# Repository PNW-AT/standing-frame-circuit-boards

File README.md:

https://github.com/PNW-AT/standing-frame-circuit-boards

https://github.com/PNW-AT/standing-frame

# Acknowledgements 
* Made using a [PJRC Teensy 4.1](https://www.pjrc.com/store/teensy41.html)
* https://github.com/XenGi/teensy.pretty
* https://github.com/XenGi/teensy_library

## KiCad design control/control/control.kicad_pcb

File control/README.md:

PCB CAD for the user interface panel

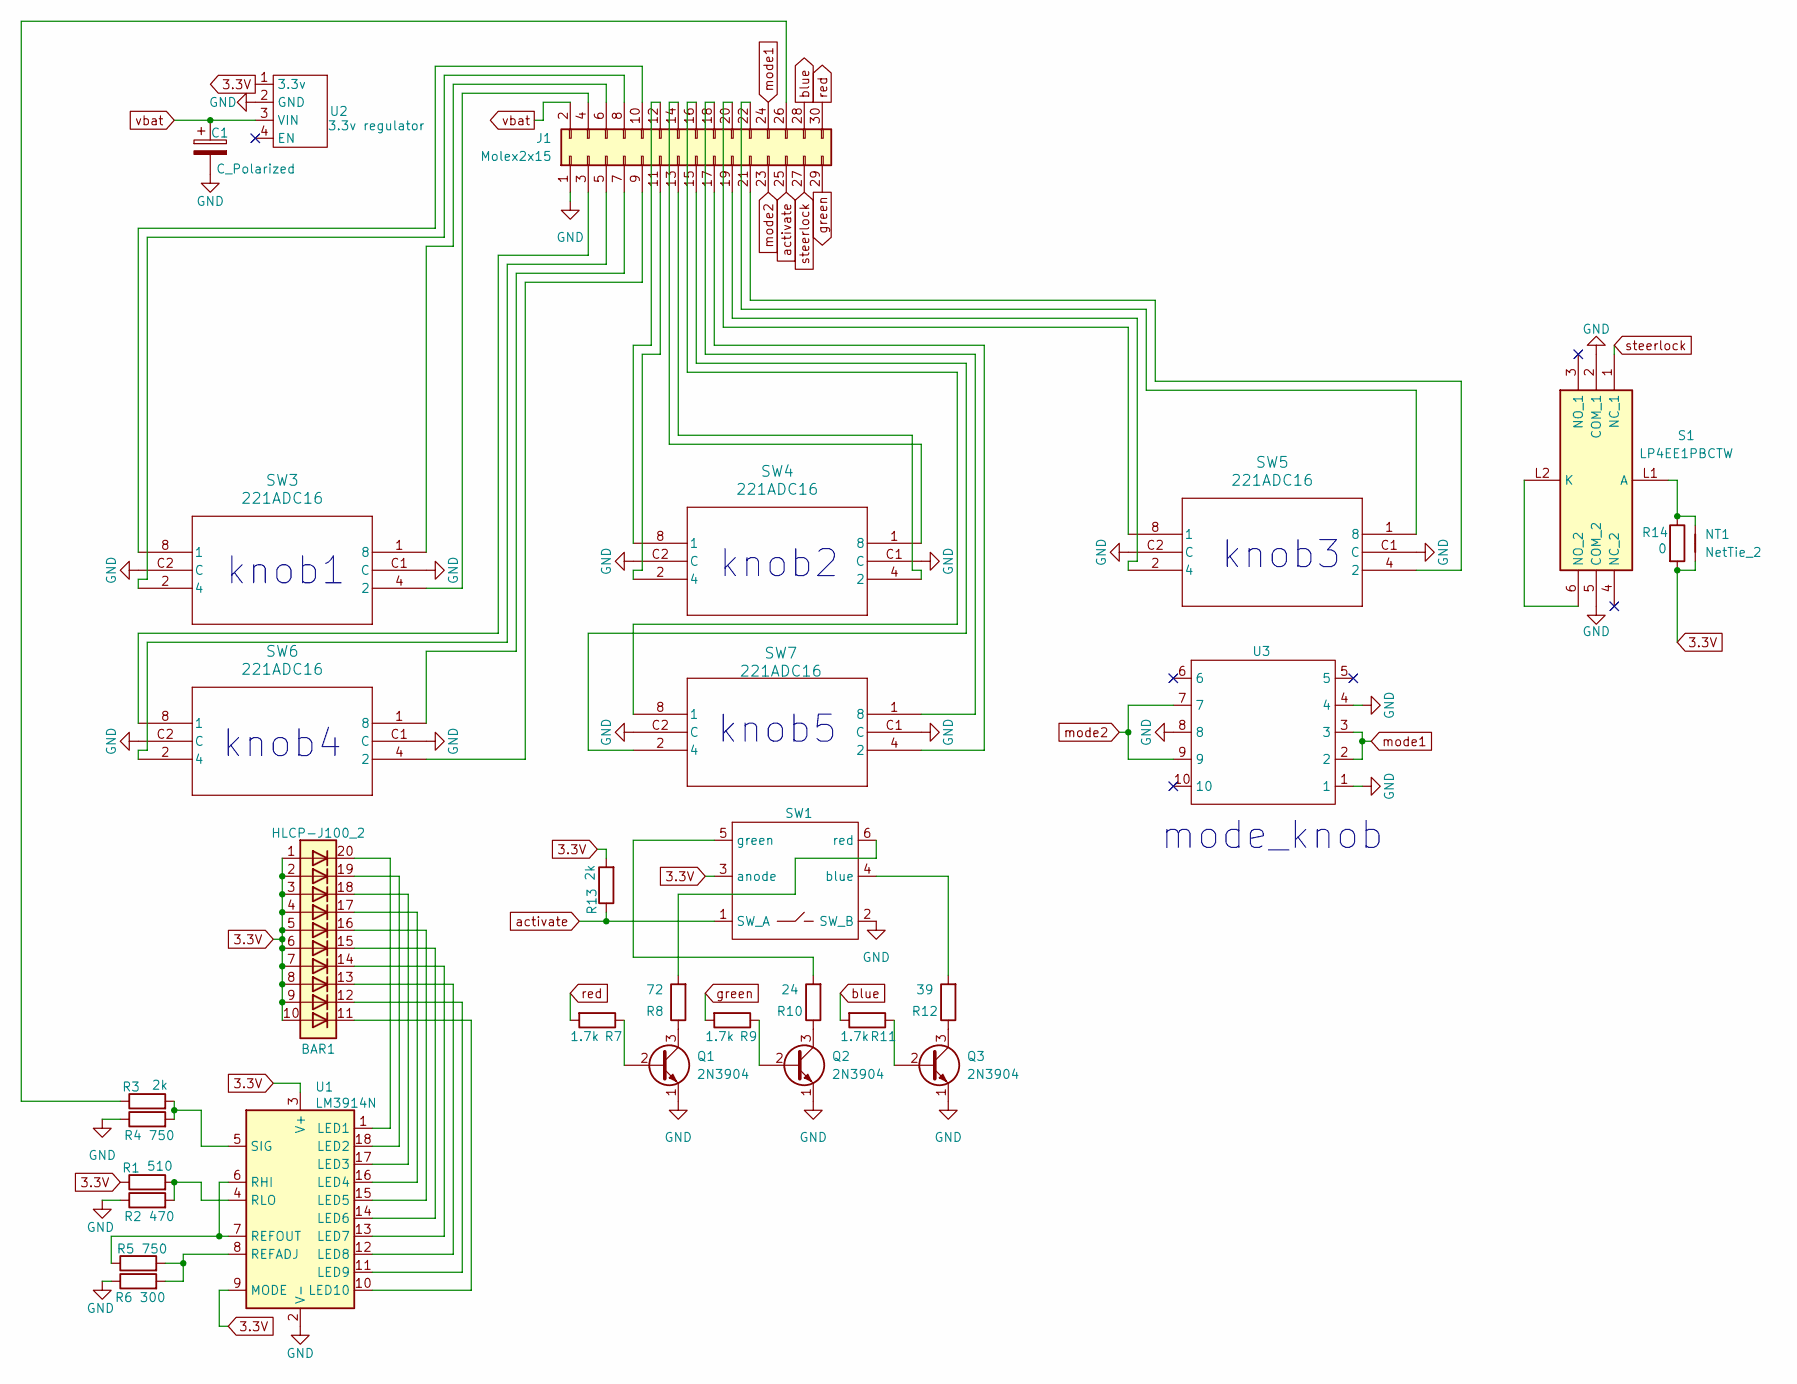
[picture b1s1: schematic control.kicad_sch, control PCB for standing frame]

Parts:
BAR1: HLCP-J100_2; HLCP-J100
C1: C_Polarized; C_Radial_D8.0mm_H11.5mm_P3.50mm
J1: Molex2x15; CON_702463001_MOL_molex2x15
NT1: NetTie_2; SolderJumper-2_P1.3mm_Bridged_RoundedPad1.0x1.5mm
Q1, Q2, Q3: 2N3904; TO-92_Inline
R1: 510; R_Axial_DIN0207_L6.3mm_D2.5mm_P10.16mm_Horizontal
R2: 470; R_Axial_DIN0207_L6.3mm_D2.5mm_P10.16mm_Horizontal
R3, R13: 2k; R_Axial_DIN0207_L6.3mm_D2.5mm_P10.16mm_Horizontal
R4, R5: 750; R_Axial_DIN0207_L6.3mm_D2.5mm_P10.16mm_Horizontal
R6: 300; R_Axial_DIN0207_L6.3mm_D2.5mm_P10.16mm_Horizontal
R7, R9, R11: 1.7k; R_Axial_DIN0207_L6.3mm_D2.5mm_P10.16mm_Horizontal
R8: 72; R_Axial_DIN0207_L6.3mm_D2.5mm_P10.16mm_Horizontal
R10: 24; R_Axial_DIN0207_L6.3mm_D2.5mm_P10.16mm_Horizontal
R12: 39; R_Axial_DIN0207_L6.3mm_D2.5mm_P10.16mm_Horizontal
R14: 0; R_Axial_DIN0207_L6.3mm_D2.5mm_P10.16mm_Horizontal
S1: LP4EE1PBCTW; Manufacturer_Part_Number LP4EE1PBCTW; Mouser Part Number 612-LP4EE1PBCTW
SW1: KP0215ASAKG03RGBP-1FJB
SW3, SW4, SW5, SW6, SW7: 221ADC16
U1: LM3914N; DIP-18_W7.62mm
U2: 3.3v regulator; pololu4964_3.3v
U3: R20405RN02Q

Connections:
3.3V: BAR1.1 (A), BAR1.2 (A), BAR1.3 (A), BAR1.4 (A), BAR1.5 (A), BAR1.6 (A), BAR1.7 (A), BAR1.8 (A), BAR1.9 (A), BAR1.10 (A), NT1.1, R1.1, R13.2, R14.2, SW1.3 (anode), U1.3 (V+), U1.9 (MODE), U2.1 (3.3v)
GND: C1.2, J1.1, Q1.1 (E), Q2.1 (E), Q3.1 (E), R2.1, R4.1, R6.1, S1.2 (COM_1), S1.5 (COM_2), SW1.2 (SW_B), SW3.C1 (C), SW3.C2 (C), SW4.C1 (C), SW4.C2 (C), SW5.C1 (C), SW5.C2 (C), SW6.C1 (C), SW6.C2 (C), SW7.C1 (C), SW7.C2 (C), U1.2 (V-), U2.2 (GND), U3.1, U3.4, U3.8
unnamed: J1.3, SW6.8 (1)
unnamed: J1.4, SW3.4 (2)
unnamed: J1.5, SW6.2 (4)
unnamed: J1.6, SW3.1 (8)
unnamed: J1.7, SW6.1 (8)
unnamed: J1.8, SW3.2 (4)
unnamed: J1.9, SW6.4 (2)
unnamed: J1.10, SW3.8 (1)
unnamed: J1.11, SW4.2 (4)
unnamed: J1.12, SW4.8 (1)
unnamed: J1.13, SW4.4 (2)
unnamed: J1.14, SW4.1 (8)
unnamed: J1.15, SW7.2 (4)
unnamed: J1.16, SW7.8 (1)
unnamed: J1.17, SW7.4 (2)
unnamed: J1.18, SW7.1 (8)
unnamed: J1.19, SW5.2 (4)
unnamed: J1.20, SW5.8 (1)
unnamed: J1.21, SW5.4 (2)
unnamed: J1.22, SW5.1 (8)
unnamed: J1.26, R3.1
unnamed: Q1.2 (B), R7.1
unnamed: Q1.3 (C), R8.1
unnamed: Q2.2 (B), R9.1
unnamed: Q2.3 (C), R10.1
unnamed: Q3.2 (B), R11.1
unnamed: Q3.3 (C), R12.1
unnamed: NT1.2, R14.1, S1.L1 (A)
unnamed: S1.6 (NO_2), S1.L2 (K)
unnamed: R12.2, SW1.4 (blue)
unnamed: R10.2, SW1.5 (green)
unnamed: R8.2, SW1.6 (red)
unnamed: BAR1.20 (K), U1.1 (LED1)
unnamed: BAR1.19 (K), U1.18 (LED2)
unnamed: BAR1.18 (K), U1.17 (LED3)
unnamed: BAR1.17 (K), U1.16 (LED4)
unnamed: BAR1.16 (K), U1.15 (LED5)
unnamed: BAR1.15 (K), U1.14 (LED6)
unnamed: BAR1.14 (K), U1.13 (LED7)
unnamed: BAR1.13 (K), U1.12 (LED8)
unnamed: BAR1.12 (K), U1.11 (LED9)
unnamed: BAR1.11 (K), U1.10 (LED10)
unnamed: R5.2, R6.2, U1.8 (REFADJ)
unnamed: R5.1, U1.6 (RHI), U1.7 (REFOUT)
unnamed: R1.2, R2.2, U1.4 (RLO)
unnamed: R3.2, R4.2, U1.5 (SIG)
activate: J1.25, R13.1, SW1.1 (SW_A)
blue: J1.28, R11.2
green: J1.29, R9.2
mode1: J1.24, U3.2, U3.3
mode2: J1.23, U3.7, U3.9
red: J1.30, R7.2
steerlock: J1.27, S1.1 (NC_1)
vbat: C1.1, J1.2, U2.3 (VIN)

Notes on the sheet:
knob2
knob4
knob5
knob3
mode_knob
knob1

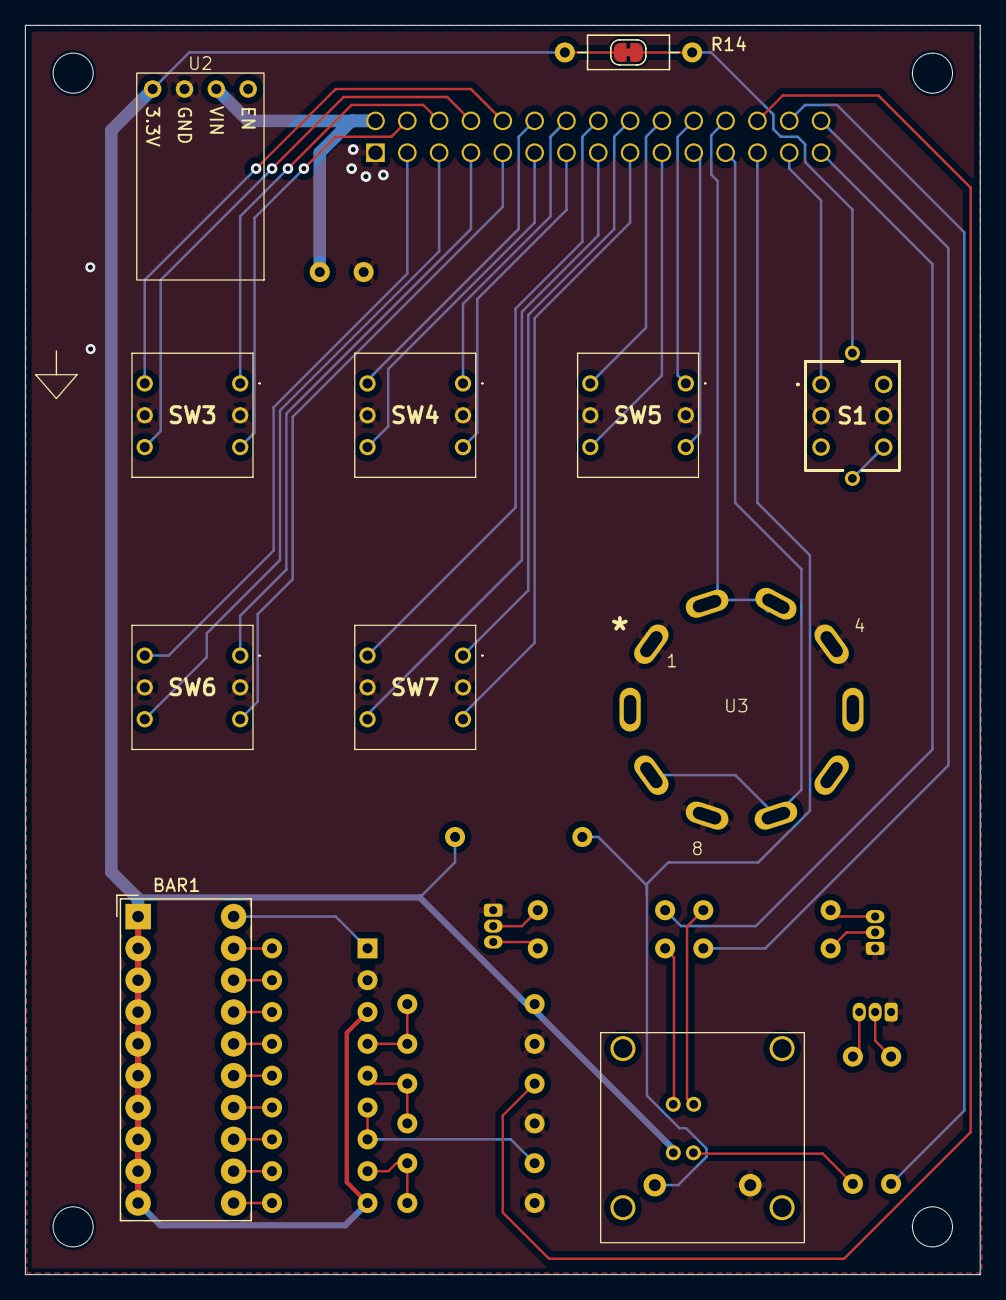
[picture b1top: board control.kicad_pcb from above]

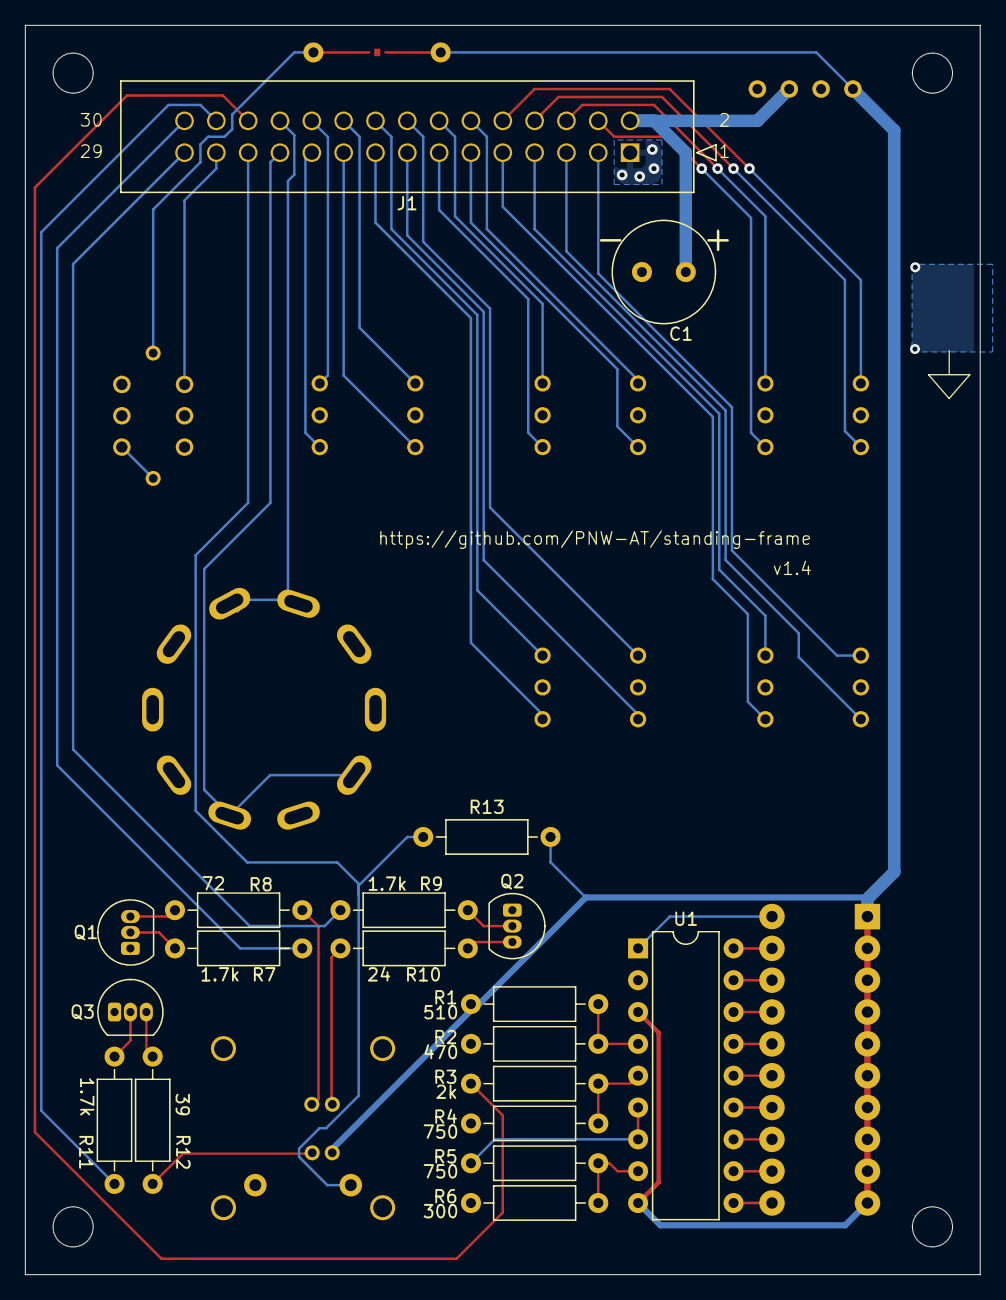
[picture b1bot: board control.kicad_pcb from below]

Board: 2 copper layers, 76.2 x 99.7 mm, 31 parts (18 on the bottom side), 56 nets.

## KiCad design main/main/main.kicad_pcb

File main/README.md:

PCB CAD for the central board with the Teensy

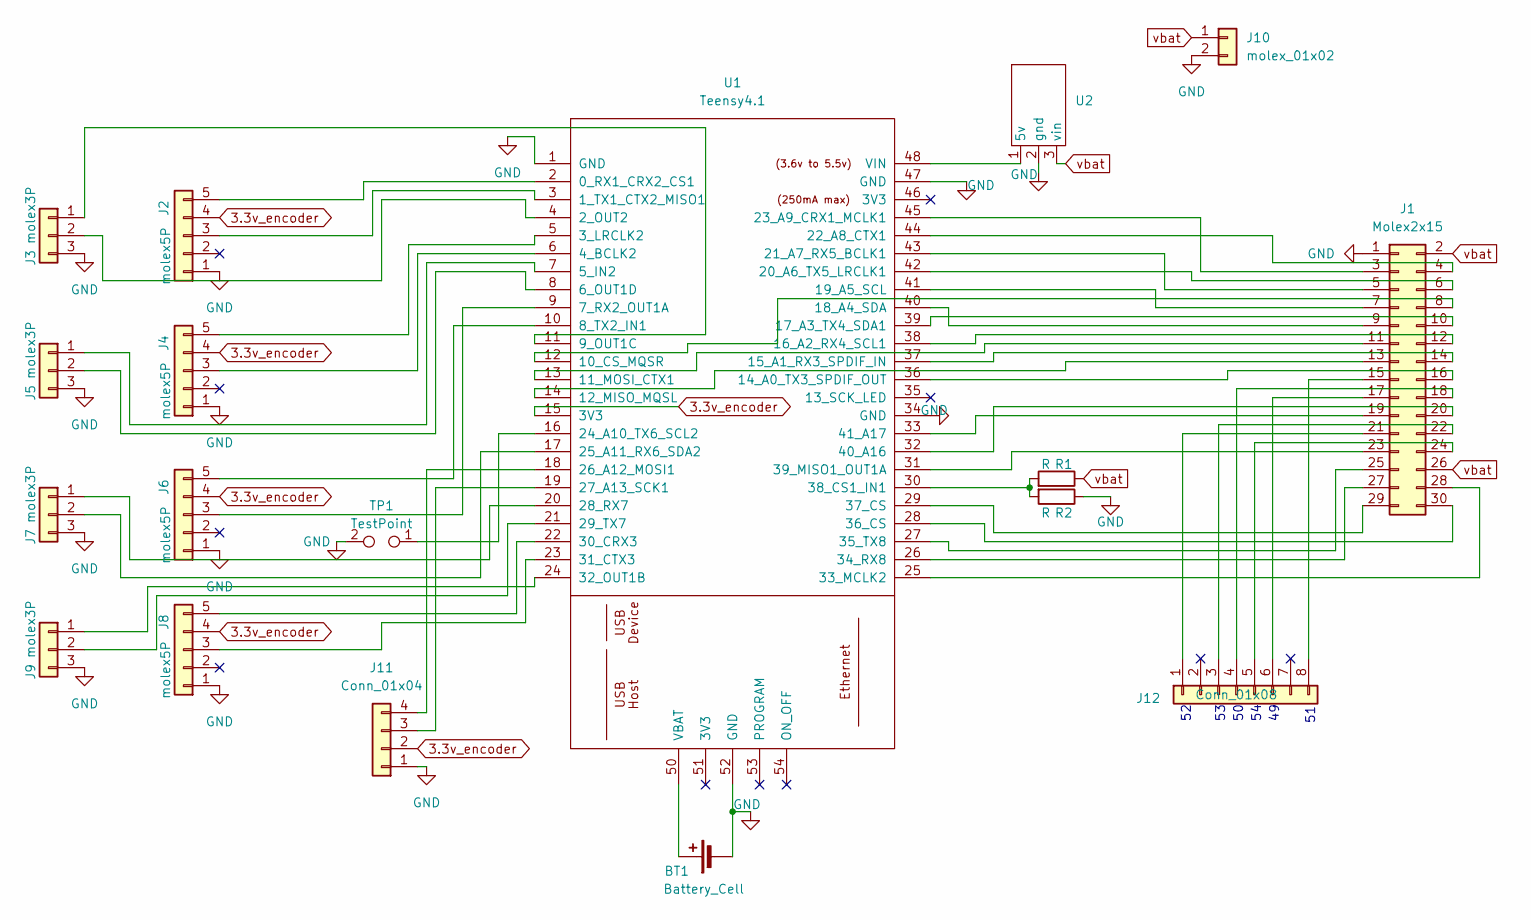
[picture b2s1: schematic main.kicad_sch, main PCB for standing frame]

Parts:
BT1: Battery_Cell; TestPoint_2Pads_Pitch2.54mm_Drill0.8mm
J1: Molex2x15; CON_702463001_MOL_molex2x15
J2, J4, J6, J8: molex5P; Molex_SL_171971-0005_1x05_P2.54mm_Vertical
J3, J5, J7, J9: molex3P; Molex_SL_171971-0003_1x03_P2.54mm_Vertical
J10: molex_01x02; Molex_SL_171971-0002_1x02_P2.54mm_Vertical
J11: Conn_01x04; Molex_SL_171971-0004_1x04_P2.54mm_Vertical
J12: Conn_01x08; PinSocket_2x04_P1.27mm_Vertical
R1, R2: R; R_Axial_DIN0204_L3.6mm_D1.6mm_P5.08mm_Horizontal
TP1: TestPoint; TestPoint_2Pads_Pitch2.54mm_Drill0.8mm
U1: Teensy4.1; Teensy41
U2: pololu4085

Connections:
3.3v_encoder: J2.4, J4.4, J6.4, J8.4, J11.2, U1.15 (3V3)
GND: BT1.2 (-), J1.1, J2.1, J3.3, J4.1, J5.3, J6.1, J7.3, J8.1, J9.3, J10.2, J11.1, R2.1, TP1.2, U1.1 (GND), U1.34 (GND), U1.47 (GND), U1.52 (GND), U2.2 (gnd)
unnamed: BT1.1 (+), U1.50 (VBAT)
unnamed: J1.3, U1.45 (23_A9_CRX1_MCLK1)
unnamed: J1.4, U1.44 (22_A8_CTX1)
unnamed: J1.5, U1.43 (21_A7_RX5_BCLK1)
unnamed: J1.6, U1.42 (20_A6_TX5_LRCLK1)
unnamed: J1.7, U1.41 (19_A5_SCL)
unnamed: J1.8, U1.12 (10_CS_MQSR)
unnamed: J1.9, U1.40 (18_A4_SDA)
unnamed: J1.10, U1.39 (17_A3_TX4_SDA1)
unnamed: J1.11, U1.13 (11_MOSI_CTX1)
unnamed: J1.12, U1.38 (16_A2_RX4_SCL1)
unnamed: J1.13, U1.14 (12_MISO_MQSL)
unnamed: J1.14, U1.37 (15_A1_RX3_SPDIF_IN)
unnamed: J1.15, J12.8
unnamed: J1.16, U1.36 (14_A0_TX3_SPDIF_OUT)
unnamed: J1.17, J12.6
unnamed: J1.18, J12.4
unnamed: J1.19, U1.33 (41_A17)
unnamed: J1.20, U1.32 (40_A16)
unnamed: J1.21, J12.1
unnamed: J1.22, J12.3
unnamed: J1.23, U1.31 (39_MISO1_OUT1A)
unnamed: J1.24, J12.5
unnamed: J1.25, U1.27 (35_TX8)
unnamed: J1.27, U1.26 (34_RX8)
unnamed: J1.28, U1.25 (33_MCLK2)
unnamed: J1.29, U1.29 (37_CS)
unnamed: J1.30, U1.28 (36_CS)
unnamed: J2.3, U1.3 (1_TX1_CTX2_MISO1)
unnamed: J2.5, U1.2 (0_RX1_CRX2_CS1)
unnamed: J3.1, U1.11 (9_OUT1C)
unnamed: J3.2, U1.4 (2_OUT2)
unnamed: J4.3, U1.6 (4_BCLK2)
unnamed: J4.5, U1.5 (3_LRCLK2)
unnamed: J5.1, U1.7 (5_IN2)
unnamed: J5.2, U1.8 (6_OUT1D)
unnamed: J6.3, U1.9 (7_RX2_OUT1A)
unnamed: J6.5, U1.10 (8_TX2_IN1)
unnamed: J7.1, U1.20 (28_RX7)
unnamed: J7.2, U1.17 (25_A11_RX6_SDA2)
unnamed: J8.3, U1.23 (31_CTX3)
unnamed: J8.5, U1.22 (30_CRX3)
unnamed: J9.1, U1.24 (32_OUT1B)
unnamed: J9.2, U1.21 (29_TX7)
unnamed: J11.3, U1.19 (27_A13_SCK1)
unnamed: J11.4, U1.18 (26_A12_MOSI1)
unnamed: TP1.1, U1.16 (24_A10_TX6_SCL2)
unnamed: R1.2, R2.2, U1.30 (38_CS1_IN1)
unnamed: U1.48 (VIN), U2.1 (5v)
vbat: J1.2, J1.26, J10.1, R1.1, U2.3 (vin)

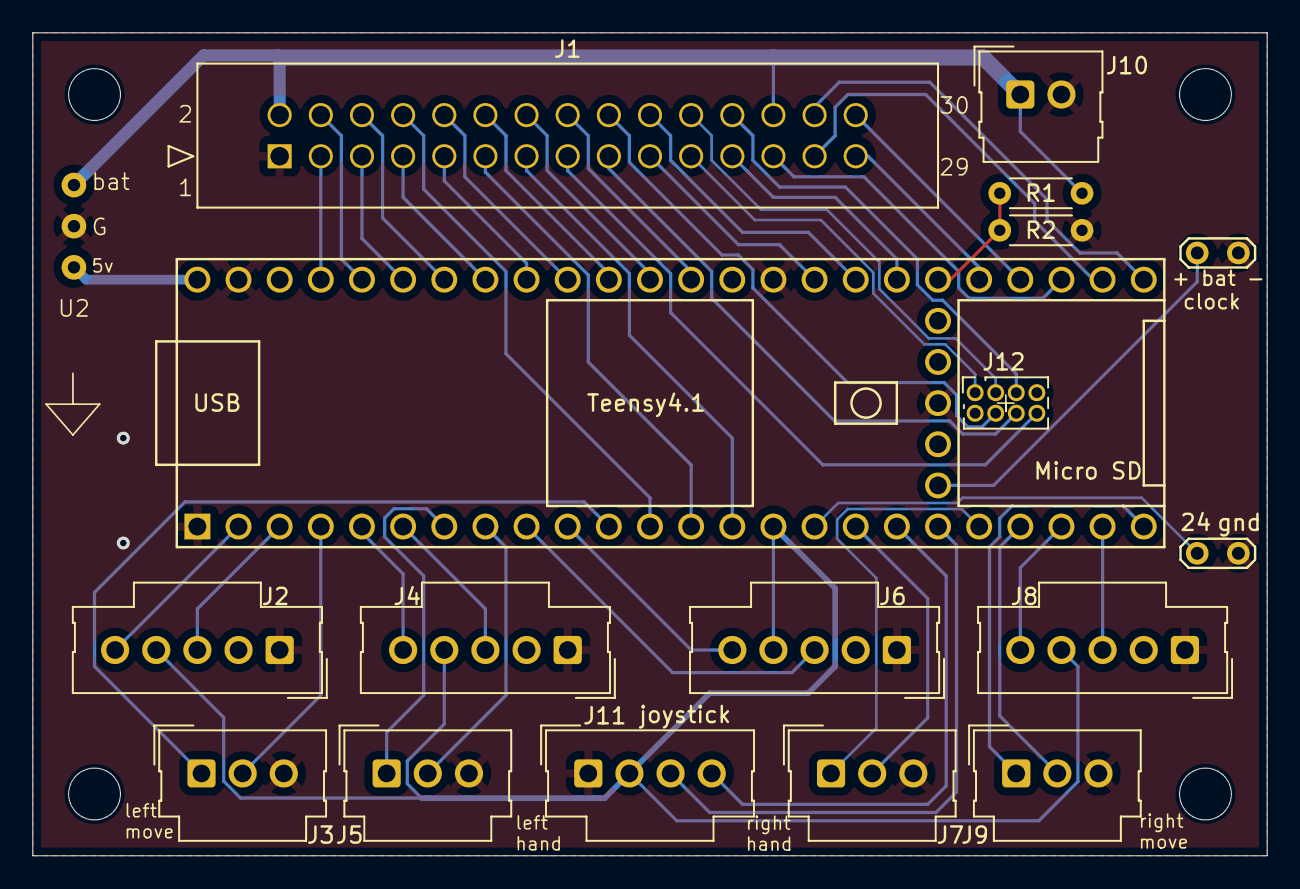
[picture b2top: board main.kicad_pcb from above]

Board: 2 copper layers, 76.2 x 50.8 mm, 18 parts (0 on the bottom side), 52 nets.

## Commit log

2024-07-02 Create control-box-PCB
2024-07-02 Rename control-box-PCB to control-box-PCBs
2024-07-02 Rename control-box-PCBs to control-box-PCB/README.md
2024-07-02 make folders
2024-07-02 start main KICAD and import teensy
2024-07-04 working on main pcb (teensy, plugs, encoder traces)
2024-07-08 working on control pcb
2024-07-08 add joystick plug, adjust resistors
2024-07-10 control pcb almost done
2024-07-10 main fully routed
2024-07-10 change plug for extra pns
2024-07-10 final adjustments for v1.0
2024-07-10 export gerbers and schematic
2024-07-11 update v1.0 gerbers
2024-07-11 v1.0
2024-07-20 v1.4
2024-07-29 add step files
